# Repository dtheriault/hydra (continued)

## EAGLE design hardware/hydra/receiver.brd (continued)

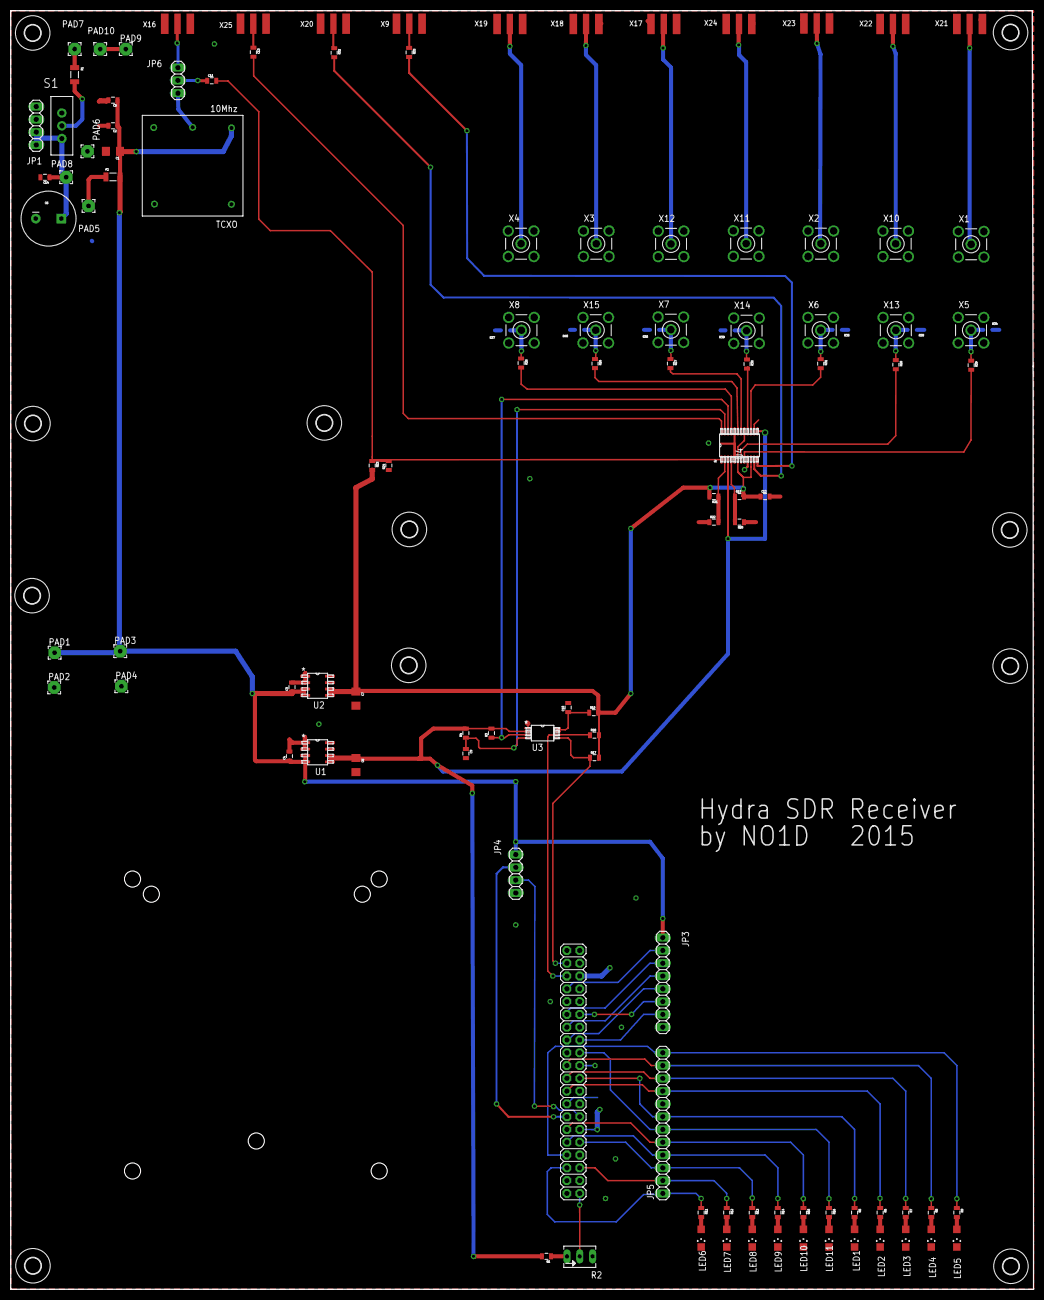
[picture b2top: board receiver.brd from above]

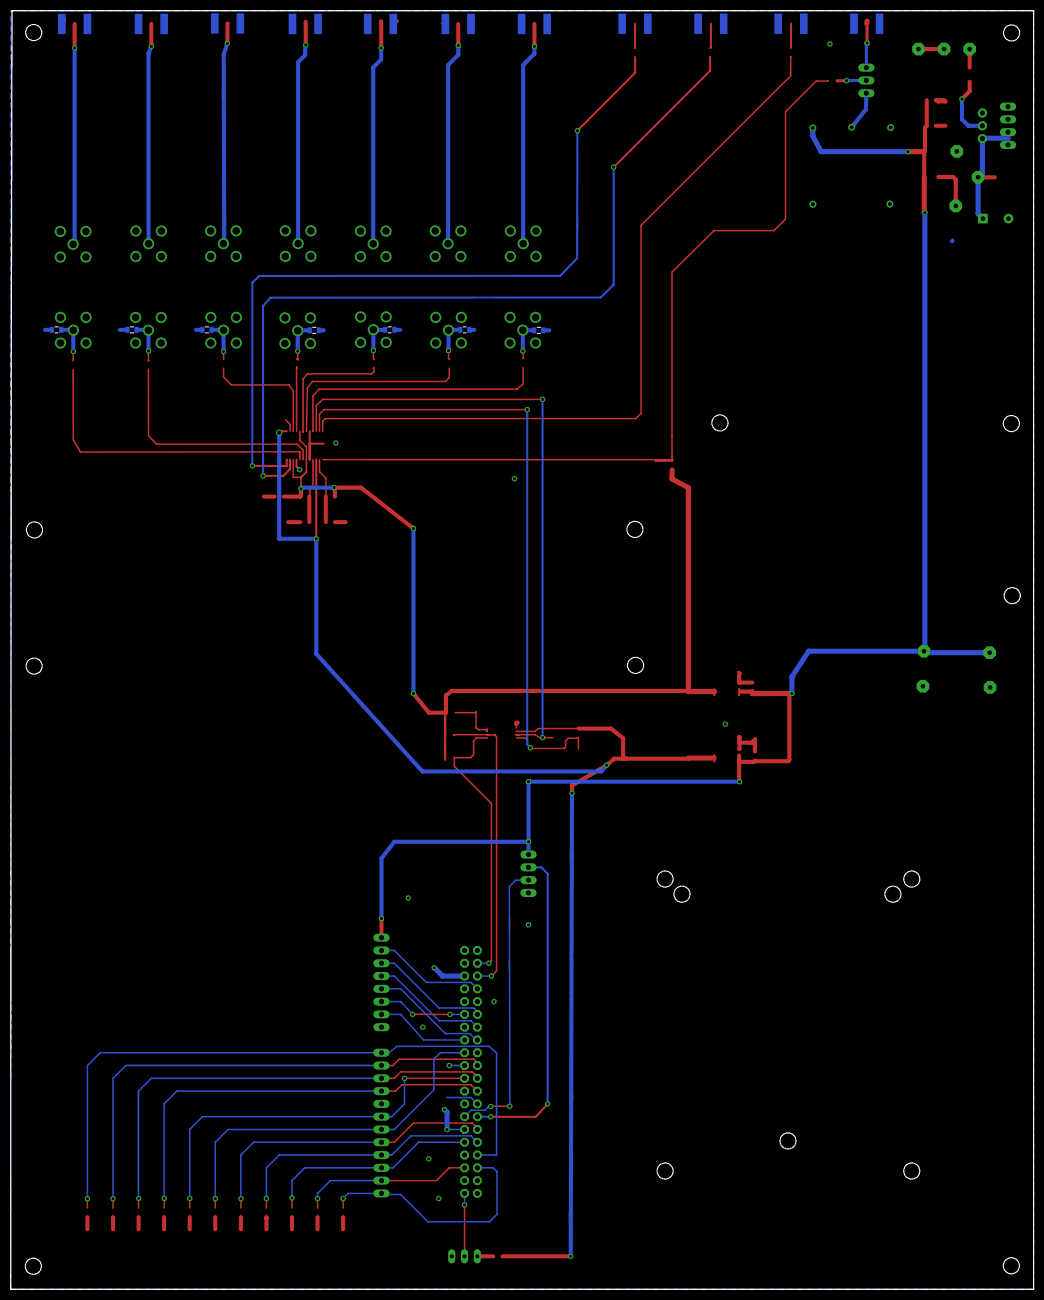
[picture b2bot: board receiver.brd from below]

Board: 2 copper layers, 203.2 x 254.0 mm, 125 parts (7 on the bottom side), 79 nets.

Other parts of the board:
U$2, U$3, U$4, U$5, U$6, U$7, U$8, U$9, U$13, U$14, U$15: 3,2

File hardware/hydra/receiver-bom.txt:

Partlist exported from /home/doug/eagle/Hydra/receiver.sch at 6/20/15 10:13 AM

Qty Value            Device            Package                Parts                                                              Description                      
11                   LEDCHIPLED_1206   CHIPLED_1206           LED1, LED2, LED3, LED4, LED5, LED6, LED7, LED8, LED9, LED10, LED11 LED                              
14                   LTI-SASF54GT      LTI-SASF54GT           X1, X2, X3, X4, X5, X6, X7, X8, X10, X11, X12, X13, X14, X15       SMA vertical PCB thrue hole jack 
1                    PINHD-1X4         1X04                   JP1                                                                PIN HEADER                       
1                    PTCSMD            PTC-1206               F2                                                                 Resettable Fuse PTC              
11                   SMACONNECTOR_EDGE SMA_EDGELAUNCH         X9, X16, X17, X18, X19, X20, X21, X22, X23, X24, X25               SMA Connector                    
1                    SWITCH-SPDTPTH    SWITCH-SPDT            S1                                                                 SPDT Switch                      
10                   WIREPAD2,54/0,9   2,54/0,9               PAD1, PAD2, PAD3, PAD4, PAD5, PAD6, PAD7, PAD8, PAD9, PAD10        Wire PAD connect wire on PCB     
5   .1uf             CAP0805           0805                   C2, C3, C4, C10, C12                                               Capacitor                        
2   10 uF            CAP1206           1206                   C7, C8                                                             Capacitor                        
2   100              RESISTOR0805-RES  0805                   R23, R24                                                           Resistor                         
1   100 uF           CAP_POLPTH4       CPOL-RADIAL-1000UF-25V C6                                                                 Capacitor Polarized              
1   100k             RESISTOR0805-RES  0805                   R10                                                                Resistor                         
2   10k              RESISTOR0805-RES  0805                   R3, R4                                                             Resistor                         
1   10k              TRIM_EU-B64Y      B64Y                   R2                                                                 POTENTIOMETER                    
2   10nf             CAP0805           0805                   C11, C13                                                           Capacitor                        
1   10uf             CAP1206           1206                   C1                                                                 Capacitor                        
5   1k               RESISTOR0805-RES  0805                   R1, R19, R20, R21, R22                                             Resistor                         
1   1nf              CAP0805           0805                   C5                                                                 Capacitor                        
9   22               RESISTOR0805-RES  0805                   R25, R26, R27, R28, R29, R30, R31, R32, R33                        Resistor                         
1   220pf            CAP0805           0805                   C9                                                                 Capacitor                        
11  330              RESISTOR0805-RES  0805                   R5, R6, R7, R8, R9, R11, R12, R13, R14, R15, R16                   Resistor                         
2   5.6k             RESISTOR0805-RES  0805                   R17, R18                                                           Resistor                         
1   Adafruit LCD     PINHD-1X4         1X04                   JP4                                                                PIN HEADER                       
1   C1_GPIO          C1_GPIO           2X20-BIG               JP2                                                                                                 
1   CDCE949_PW_24    CDCE949_PW_24     PW24                   U4                                                                                                  
1   LED Panel        PINHD-1X12        1X12                   JP5                                                                PIN HEADER                       
1   PCA9306_PW_8     PCA9306_PW_8      PW8                    U3                                                                                                  
1   PLL Clock Source PINHD-1X3         1X03                   JP6                                                                PIN HEADER                       
1   PTCSMD           PTCSMD            PTC-1206               F1                                                                 Resettable Fuse PTC              
1   TPS77518_D_8     TPS77518_D_8      D8                     U1                                                                                                  
1   TPS77533_D_8     TPS77533_D_8      D8                     U2                                                                                                  
1   TXCO 10M         TCXO-10MTHRU-HOLE THRU-HOLE              $3_194_$_2015-06-18_19-54-36                                                                        
1   oDroid LCD       PINHD-1X8         1X08                   JP3                                                                PIN HEADER

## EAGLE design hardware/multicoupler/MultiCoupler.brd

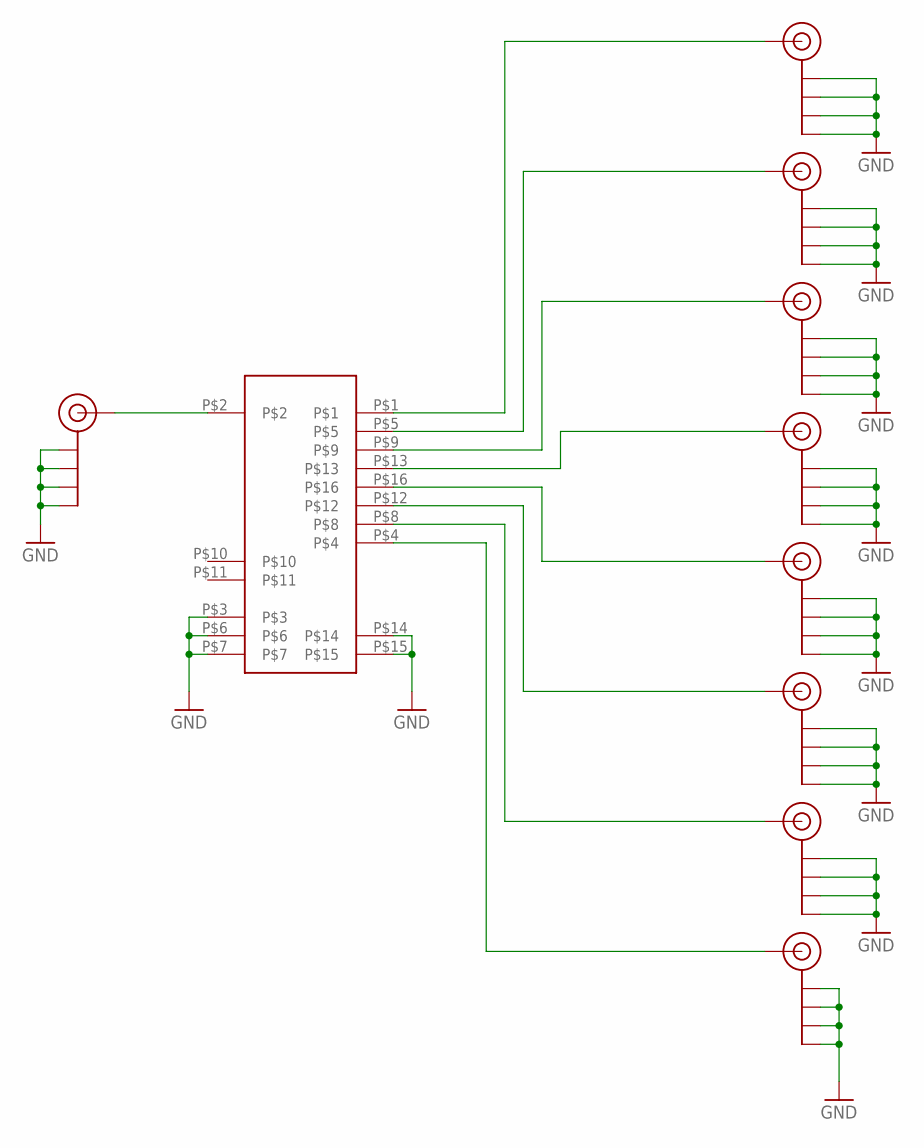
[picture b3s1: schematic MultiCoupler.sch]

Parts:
J$1, J$2, J$3, J$4, J$5, J$6, J$7, J$8, J$9: SMA_EDGE; SMA-EDGE
U$1: PSC-8-1-75THROUGH_HOLE; PSC-8-1-75

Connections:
GND: J$1.GND@0 (GND), J$1.GND@1 (GND), J$1.GND@2 (GND), J$1.GND@3 (GND), J$2.GND@0 (GND), J$2.GND@1 (GND), J$2.GND@2 (GND), J$2.GND@3 (GND), J$3.GND@0 (GND), J$3.GND@1 (GND), J$3.GND@2 (GND), J$3.GND@3 (GND), J$4.GND@0 (GND), J$4.GND@1 (GND), J$4.GND@2 (GND), J$4.GND@3 (GND), J$5.GND@0 (GND), J$5.GND@1 (GND), J$5.GND@2 (GND), J$5.GND@3 (GND), J$6.GND@0 (GND), J$6.GND@1 (GND), J$6.GND@2 (GND), J$6.GND@3 (GND), J$7.GND@0 (GND), J$7.GND@1 (GND), J$7.GND@2 (GND), J$7.GND@3 (GND), J$8.GND@0 (GND), J$8.GND@1 (GND), J$8.GND@2 (GND), J$8.GND@3 (GND), J$9.GND@0 (GND), J$9.GND@1 (GND), J$9.GND@2 (GND), J$9.GND@3 (GND), U$1.P$3, U$1.P$6, U$1.P$7, U$1.P$14, U$1.P$15
unnamed: J$1.SIG (SIGNAL), U$1.P$2
unnamed: J$9.SIG (SIGNAL), U$1.P$1
unnamed: J$8.SIG (SIGNAL), U$1.P$5
unnamed: J$7.SIG (SIGNAL), U$1.P$9
unnamed: J$2.SIG (SIGNAL), U$1.P$13
unnamed: J$3.SIG (SIGNAL), U$1.P$16
unnamed: J$4.SIG (SIGNAL), U$1.P$12
unnamed: J$5.SIG (SIGNAL), U$1.P$8
unnamed: J$6.SIG (SIGNAL), U$1.P$4

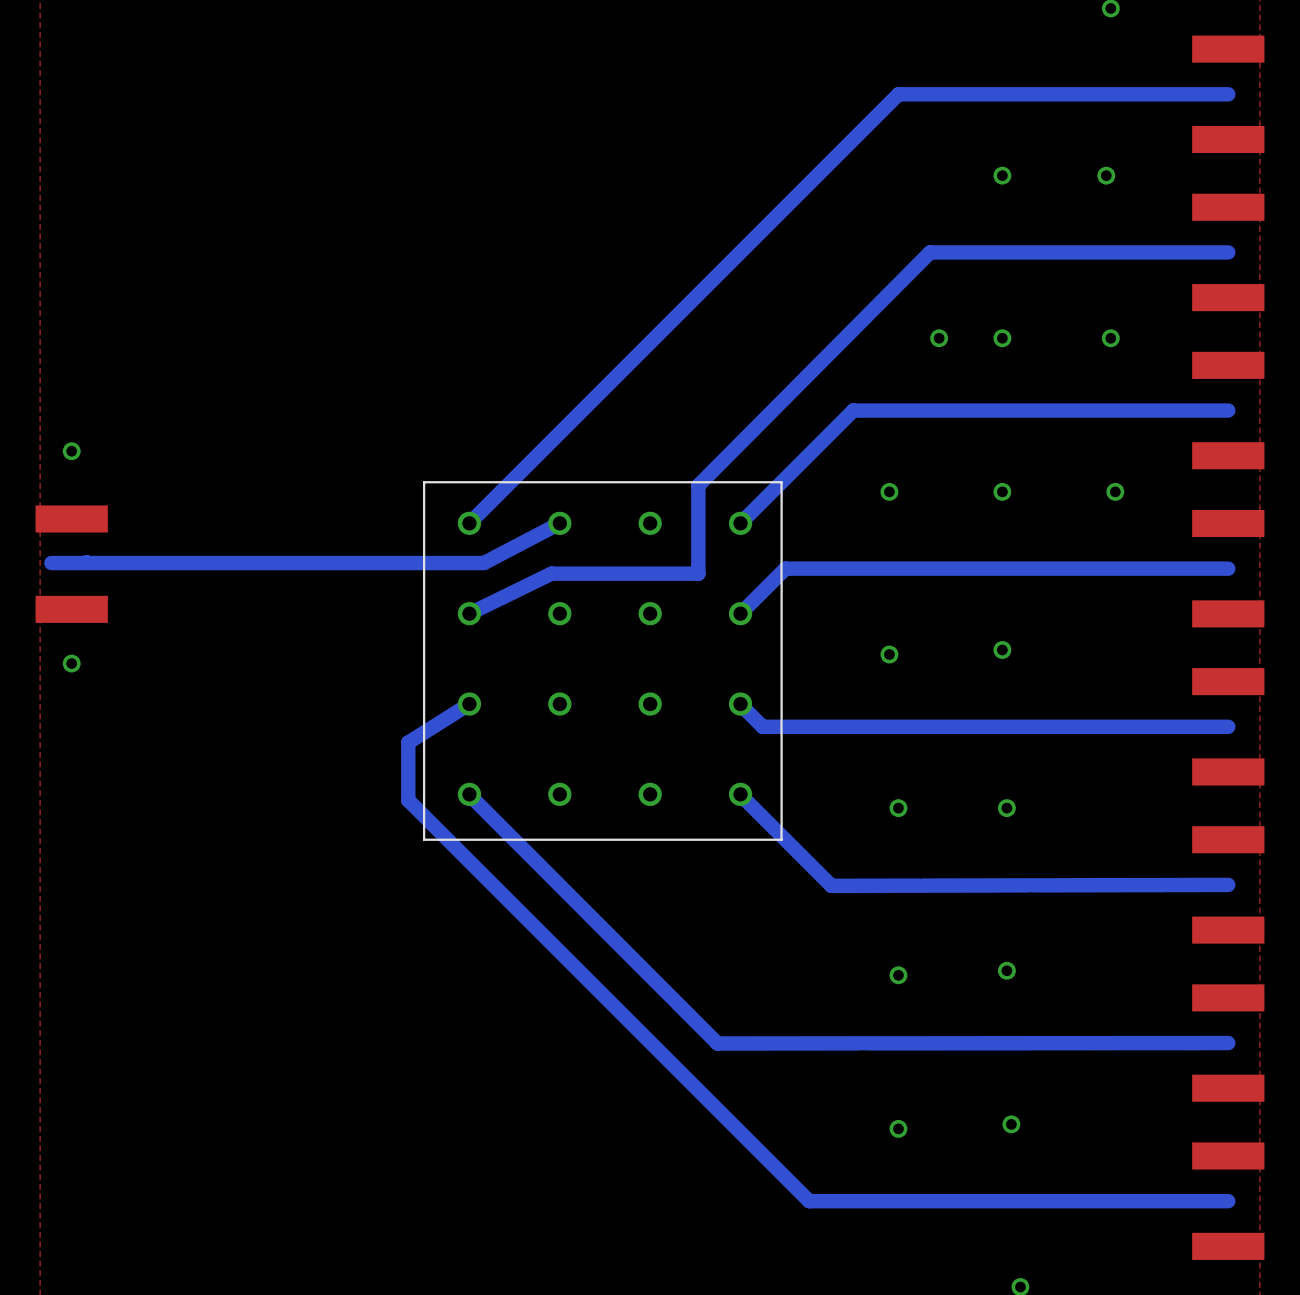
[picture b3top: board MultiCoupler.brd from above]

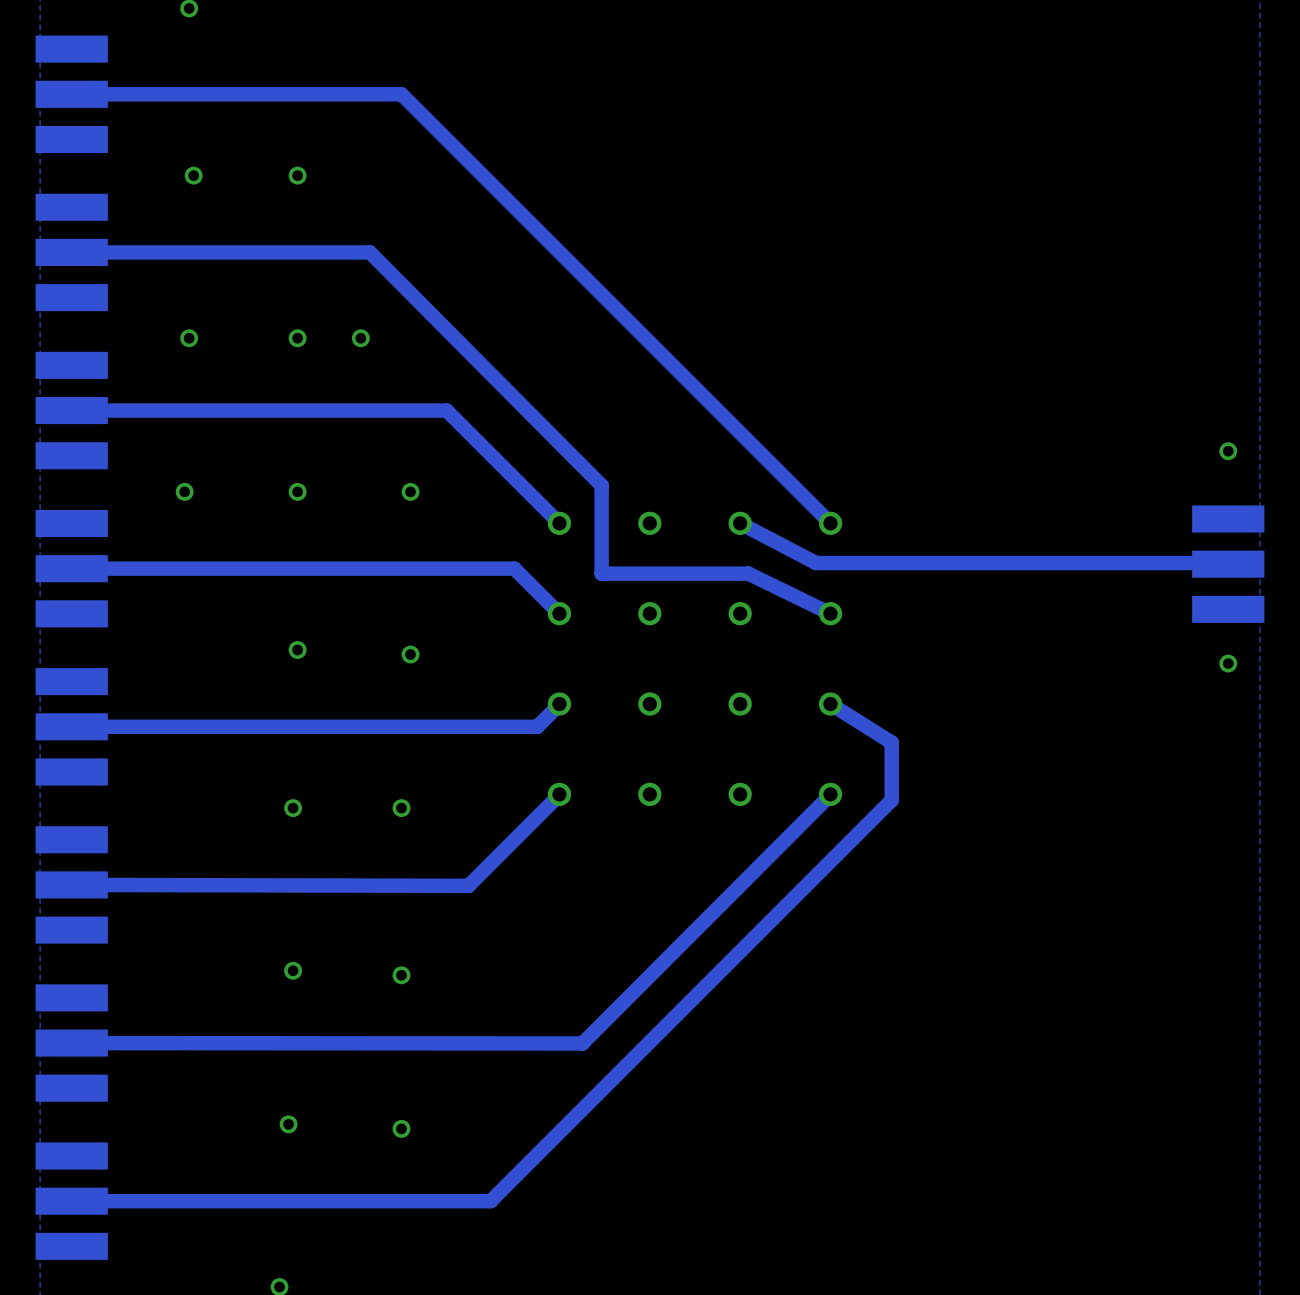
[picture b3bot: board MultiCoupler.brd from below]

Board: 2 copper layers, 10 parts (9 on the bottom side), 10 nets.

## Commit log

2014-09-23 First submit to the test repo.
2015-02-20 Updated Readme to reflect project Medusa. Repo renamed from test.
2015-02-20 Updated Readme to fix format issue. Restructured tree adding software level, hardware... Added new plotter script and initial Cache from QRZ.com lookups (may help you on lookups)
2015-02-20 Ok, delete duplicate directories now that they're moved.
2015-02-20 Adding HW directory tree and Readme
2015-02-20 Adding prototype multi-coupler board and minicircuits custom part library
2015-02-20 Added few pdf's on minicircuits components considered for project.
2015-02-22 Merged in previous released version that had the -o option. I generated a patch then applied and submitting the merged change. Haven't compiled yet, as that's done on another node.
2015-02-22 added dynamic dongle freq calibration.
2015-02-22 Made the calibration round robin fair for each dongle.
2015-02-23 added timestamps to cal and restricted cal updates to be greater than 1 bin size.
2015-02-23 minimized the delay caused by calibration and prettied up the cal log messages
2015-02-23 added freq_offset printout also on ctrl-c
2015-02-23 Fixed unmatched brace in previous submit. Compiles now :-)
2015-02-23 fixed missing bracket and added reload of config file when changed
2015-02-23 fix for bug #7, should not hang now on ctrl-c with cal enabled
2015-02-23 Addressed couple of warnings during first build.
2015-02-24 Adding basic RF Block Diagram for main board and Power Supply.
2015-02-24 Added CPU Block Diagram, updated RF Block Diagram. I plan on referencing these in an official specification document we can use for the project.
    Interesting points:
    -- 5Vdc Power supplies, current rating. Wow !
    -- Added PTT input to mute receiver (applies max ATTN)
    -- Using two 4 port USB hubs for our own board vs. COTS hub
    -- Using COTS DVB-T sticks
    -- Showing oDroid C1 COTS board
2015-02-24 Added very simple packaging diagram. Expected to change as we solidify components/design.
2015-02-24 Updated DB from weekend DX CW contest. Lots of entries :-) Included html file with javascript that mostly works. Still requires map cleanup as after hour or two crashes. Scripts are dumb, really dumb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
2015-02-24 Add simple README
2015-02-24 Fixed couple buggies like messy redirections.
2015-02-24 Using curl -s vs. trying to redirect progress message to null.
2015-02-24 Little more robustness to handle case when you get QRZ session timeouts. Changed map so prints little red circles so you can see them better.
2015-02-24 Attempt to stop flip flopping in cal, stopped cal from sometimes not working, added check for weak cal signal and warning.
2015-02-24 re-added the minimum offset change
2015-02-24 and removed debug messages
2015-02-25 Tested finally on the ARM OC1, made a few tweaks in the cal area, seeing much better results.
2015-02-25 Added cmake Module to search for FFTW3 for potential WIN32 build.
2015-02-25 Fixed reparsing conf_file, no spaces between offset!
2015-02-26 Rick, added two block diagrams as options for how we'd configure the hardware. Let me know which of the two variants you tend to like or dislike and why. tnx
2015-02-26 Added printout of new configuration when re-reading config file.
2015-02-26 Removed debug print from previous commit.
2015-02-26 Added version build time and GIT hash to keep better track of versioning.
2015-02-26 Removed orignial Cmakelists file.
2015-02-26 Added mechanism to trigger a dongle set center freq when re-parsing config file.
2015-02-26 Changed the way a new freq is available per dongle, last method could miss some.
2015-02-27 Re-did the freq change after reload of config file, last night's attempt was broken!
2015-02-28 Fixed hang on ctrl-c, added backoff of calibration cycle until eventually cal only every 30 minutes.
2015-02-28 This information helped to speed up rtl frequency changes, i.e. use only one buffer: 1 megabyte of buffers at 1 Msps will take 1 second to clear. Cut the number of buffers used to a bare minimum and 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
2015-03-02 Made a change so that weaker dongles don't get excluded from calibration, also increased RTL read buffer count to 2 since this works better on the OC1.
2015-03-02 Trying to fix formatting...
2015-03-02 More reformatting
2015-03-09 limited Wideband display to 61.44 even though max freq can be up to 961.44
2015-03-24 added 3X coeff's on the halfband filter
2015-03-25 Revert "added 3X coeff's on the halfband filter" Rick's submit inappropriately performed git add and submitted all file changes in his workspace into the repo. This undo's that commit and I will even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
    This reverts commit a306a06160a1d28ea91e259d160e7cd150528be9.
2015-03-25 This submits Rick's changes to downsample.c from a306a06160a1d28ea91e259d160e7cd150528be9 added 3X coeff's on the halfband filter
2015-03-29 fixed a bug where cal was happening per rcvr disregarding the timer
2015-03-30 using liquid_dsp for downsampling
2015-04-01 Dynamically change liquid dsp filters on RTL bandwidth.
2015-04-02 Reduced filter depth for OC1
2015-04-17 Dynamic config file change support. I had multiple versions of this support scattered around so this tries to formalize it and submit. There is new function called update_dongle() that is used to upd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
    Also added conditional when center freq changes so I don't have receivers stuck
    at 10mhz. This may not be right way to solve (thought it was previously but it
    showed back up today).
2015-04-17 Get rid of double printf of same info.
2015-04-18 Wasn't printing the freq_offset when displaying center freq. Minor fix.
2015-04-20 Added some arrays to hold last values of configuration settings. Fixed issue where center freq was being reset when changing gain as seen in cuSDR. I had to toggle freq in cuSDR to get back to center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
2015-05-13 fixed count for larger coeff's
2015-06-25 Initial submit of hardware files for Hydra. Include the Receiver and Mixer boards. Schematics, board files, initial BOM's, Eagle project files. Also includes set of Eagle library files for parts that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
    Included .pdf's of top and bottom layers of each board.
2015-06-29 Merged files from DL8AAU fork of librtlsdr a5007fb6c5ed71f6e8ef86ae59a18a552e697822
    Added support to configure IF Bandwidth. Requires update to rtl_hpsdr.conf file which
    example from prototype is included with this submit.
2015-06-29 Update to documentation tree for Hydra. Includes schematics, PCB layouts in .pdf format and the set of .pdf's for some of the components used for project.
2015-06-29 Old submit from many moons ago for the local plotter script(s). Cleaning out old workspaces and this submit should take. Then again, probably should be re-written.
    Plotter still crashes the browser after 'n' interations. Update to Cache file
    which now has like 23k entries. Unique skimmer spots valid callsigns from
    QRZ.com lookups. Woohoo.
2015-06-29 Additional plotter script submit in the cleanout of old workspaces.
2015-07-04 Adding I2C support scripts to program the CDCE949 PLL.
2015-07-04 Update to I2C Readme with more notes.
2015-08-04 Added support in rtl_hpsdr.conf to identify as Hermes or Hermes LT to work with either CW Skimmer or WSPR clients.
2016-08-03 Moving from private to public repo
2016-08-03 Project name change moving from private to public repo.
2016-08-03 Removing cache files since data derived from QRZ.com queries
